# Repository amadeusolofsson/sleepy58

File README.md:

# sleepy58 (WARNING. DONGLE STILL NOT WORKING PERFECTLY FIRMWARE. AND MY THUMB CLUSTER IS FUCKED AND IS WIRED HORRIBLY AND DOESN'S WORK CORRECTLY. NEED TO FIX ERGOGEN. ALSO THE THUMBS ARE VERY UNCOMFORTABLE)

## A low-profile 4x6 orthocolumnar wireless keyboard with a 5-key thumb cluster. 
It uses [ZMK](https://github.com/zmkfirmware/zmk) together with the Seeed Studio XIAO BLE nRF52840.
I created it using [ergogen](https://github.com/ergogen/ergogen). Putting the pcb file into kiCad and routing it.
I used some of [ceoloide's](https://github.com/ceoloide/ergogen-footprints/tree/main) footprints for ergogen.

## Required Parts

| Part name           | Count | Description and sites I bought from (Many swedish ones, just use something equivalent)                                                          |
| :-------------------| :---: | :-----------------------------------------------------------------------------------------------------------------------------------------------|
| PCBs                |   2   | Flippable so only two needed. (I bought from JLCPCB, lead-free, 2 layers)                                                                       |
| XIAO Wireless MCUs  |   3   | 1 each side (+1 if you want to use as dongle) https://www.digikey.se/en/products/detail/seeed-technology-co-ltd/102010448/16652893?so=90838492  |
| Choc Switches v1    |  58   | 58 Low Profile Choc switches (29 for each hand) https://splitkb.com/products/ambients-kailh-low-profile-choc-switches?variant=48116119830875    |
| diodes 1N4148W      |  58   | 58 SOD123 SMD Diodes https://www.digikey.se/en/products/detail/diodes-incorporated/1N4148W-7-F/814371?so=9083849                                |
| Choc Keycaps        |  58   | 58 Choc v1 Compatible Keycaps https://splitkb.com/products/blank-mbk-choc-low-profile-keycaps?variant=31811491987533                            |
| Power Switches      |   2   | For switching battery power https://www.electrokit.com/en/skjutomkopplare-mini-1-pol-on-on-smd                                                  |
| JST Plugs           |   2   | For connecting battery easily https://www.electrokit.com/stiftlist-ph-2-pol-2.0mm-vinklad-1                                                     |
| Lipo batteries      |   2   | Small battery https://www.electrokit.com/batteri-lipo-3.7v-380mah                                                                               |
| Rubber feet         |  8    | Since no case https://www.electrokit.com/3m-bumpon-gummifot-6.4x1.9mm-8-pack                                                                    |
| Dongle casing       |   1   | Optional casing for dongle https://www.printables.com/model/522586-seeed-xiao-ble-case                                                          | 

## Recognitions and thanks
Ben Vallack and Christian Selig for inspiration.
@GEIGEIGEIST & @Pipshag as great examples to compare my own keyboard with for when I got stuck on a specific part.
@VOID for the 3d printed dongle casing files.
And finally massive thanks to the ZMK & Absolem Club discords and it's members who helped me with my stupid questions :)

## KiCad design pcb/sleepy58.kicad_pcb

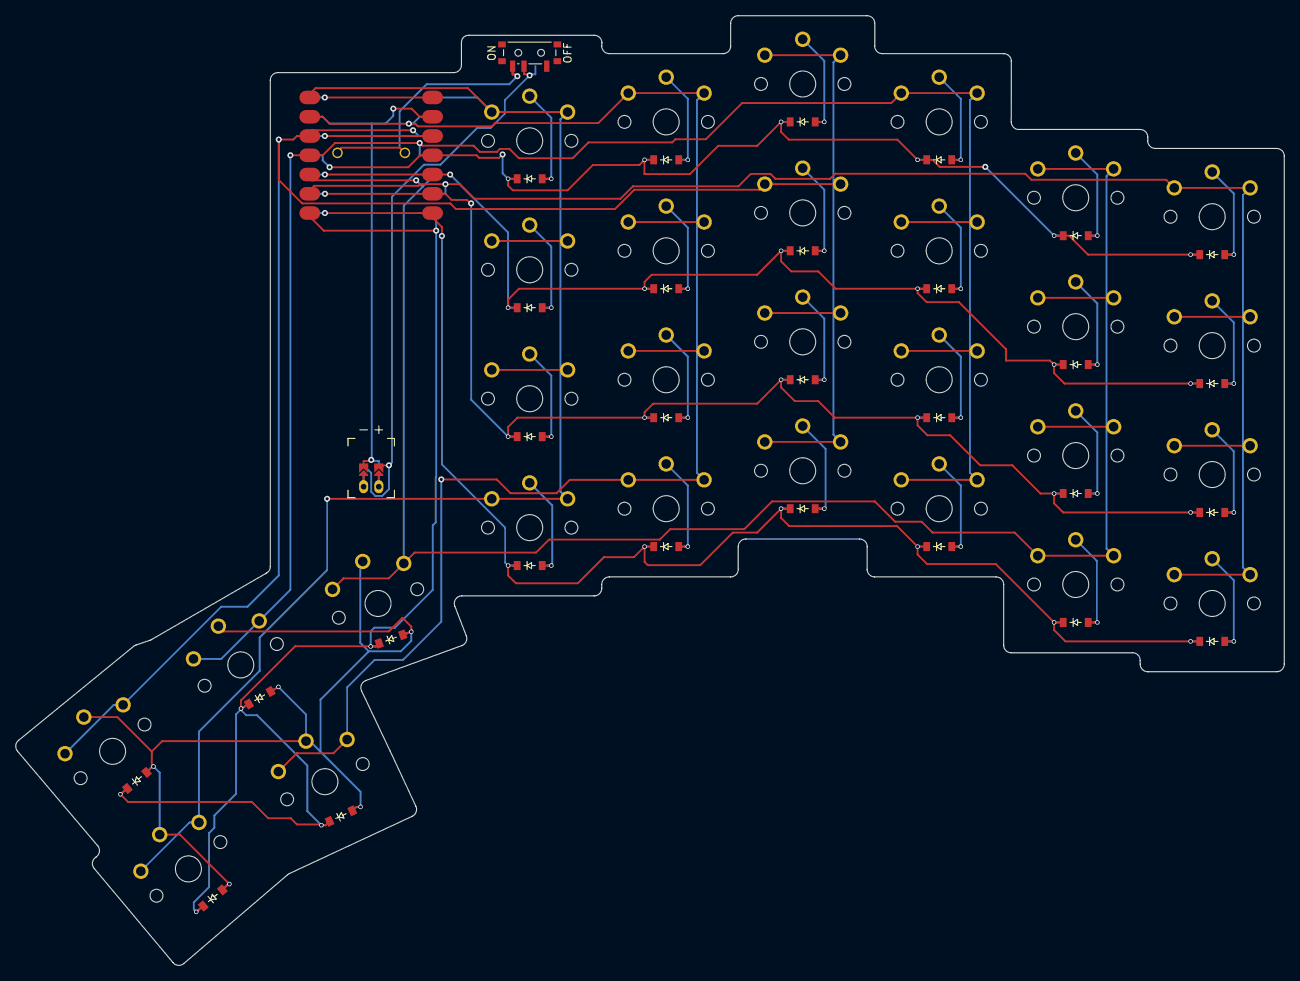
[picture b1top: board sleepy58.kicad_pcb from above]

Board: 2 copper layers, 167.3 x 125.2 mm, 61 parts (0 on the bottom side), 41 nets.

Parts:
D1, D2, D3, D4, D5, D6, D7, D8, D9, D10, D11, D12, D13, D14, D15, D16, D17, D18, D19, D20, D21, D22, D23, D24, D25, D26, D27, D28, D29: diode_tht_sod123
JST1: battery_connector_jst_ph_2
MCU1: xiao-ble-smd-reversible
PWR1: power_switch_smd_side
S1, S2, S3, S4, S5, S6, S7, S8, S9, S10, S11, S12, S13, S14, S15, S16, S17, S18, S19, S20, S21, S22, S23, S24, S25, S26, S27, S28, S29: PG1350

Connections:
BBAT+: JST1.1, PWR1.2
C0: MCU1.1, S1.1, S2.1, S3.1, S4.1, S29.1
C1: MCU1.2, S5.1, S6.1, S7.1, S8.1, S28.1
C2: MCU1.3, S9.1, S10.1, S11.1, S12.1, S27.1
C3: MCU1.4, S13.1, S14.1, S15.1, S16.1, S26.1
C4: MCU1.5, S17.1, S18.1, S19.1, S20.1, S25.1
C5: MCU1.6, S21.1, S22.1, S23.1, S24.1
GND: JST1.2, MCU1.13
JST1_1: JST1.11, JST1.21, JST1.31
JST1_2: JST1.12, JST1.22, JST1.32
R0: D25.1, D26.1, D27.1, D28.1, D29.1, MCU1.7
R1: D1.1, D5.1, D9.1, D13.1, D17.1, D21.1, MCU1.8
R2: D2.1, D6.1, D10.1, D14.1, D18.1, D22.1, MCU1.9
R3: D3.1, D7.1, D11.1, D15.1, D19.1, D23.1, MCU1.10
R4: D4.1, D8.1, D12.1, D16.1, D20.1, D24.1, MCU1.11
XBAT+: MCU1.19, PWR1.1, PWR1.3
default_default: D25.2, D26.2, D27.2, D28.2, D29.2, S25.2, S26.2, S27.2, S28.2, S29.2
index_bottom: D17.2, S17.2
index_home: D18.2, S18.2
index_num: D20.2, S20.2
index_top: D19.2, S19.2
inner_bottom: D21.2, S21.2
inner_home: D22.2, S22.2
inner_num: D24.2, S24.2
inner_top: D23.2, S23.2
middle_bottom: D13.2, S13.2
middle_home: D14.2, S14.2
middle_num: D16.2, S16.2
middle_top: D15.2, S15.2
outer_bottom: D1.2, S1.2
outer_home: D2.2, S2.2
outer_num: D4.2, S4.2
outer_top: D3.2, S3.2
pinky_bottom: D5.2, S5.2
pinky_home: D6.2, S6.2
pinky_num: D8.2, S8.2
pinky_top: D7.2, S7.2
ring_bottom: D9.2, S9.2
ring_home: D10.2, S10.2
ring_num: D12.2, S12.2
ring_top: D11.2, S11.2

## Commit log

2025-02-01 Added files
2025-02-01 Copied from zmk-config
2025-02-01 Fixing actions
2025-02-01 Rename .github/workflows/build.yml to build.yaml
2025-02-01 Rename build.yaml to .github/workflows/build.yaml
2025-02-01 Moved dongle
2025-02-01 trying to move zmk
2025-02-01 Ok don't move
